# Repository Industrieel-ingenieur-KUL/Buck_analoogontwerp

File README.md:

# Buck_analoogontwerp
Buck converter project for analog design

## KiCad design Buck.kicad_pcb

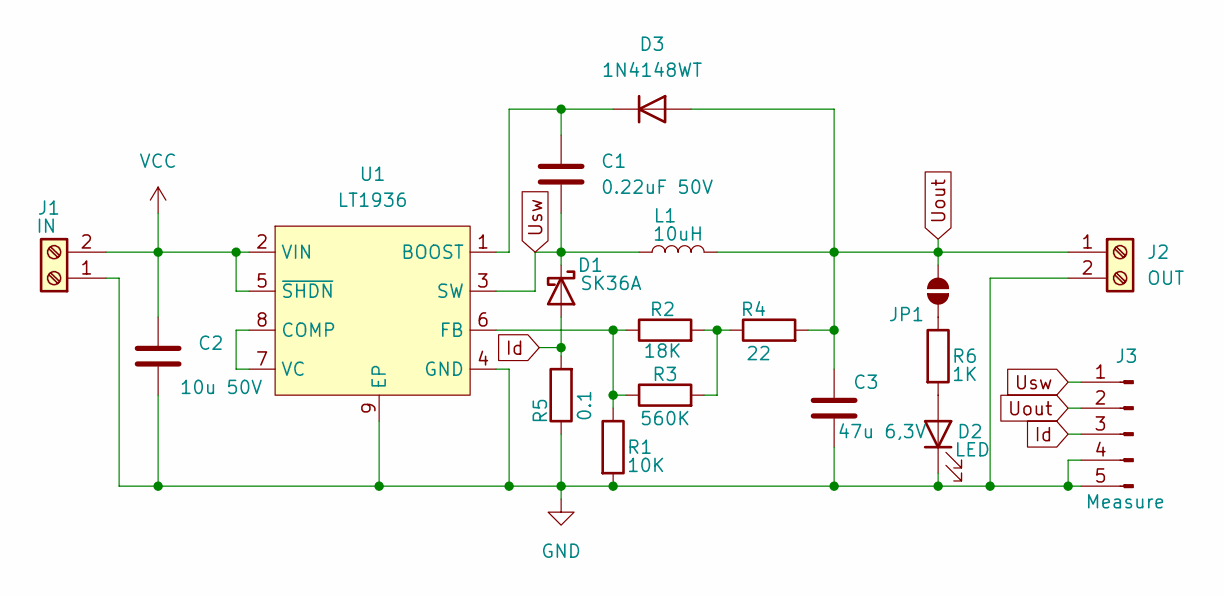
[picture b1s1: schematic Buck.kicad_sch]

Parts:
C1: 0.22uF 50V; C_0805_2012Metric_Pad1.18x1.45mm_HandSolder
C2: 10u 50V; C_1206_3216Metric_Pad1.33x1.80mm_HandSolder
C3: 47u 6,3V; C_1210_3225Metric_Pad1.33x2.70mm_HandSolder
D1: SK36A; D_SMC
D2: LED; LED_0805_2012Metric_Pad1.15x1.40mm_HandSolder
D3: 1N4148WT; D_SOD-523
J1: IN; TerminalBlock_MaiXu_MX126-5.0-02P_1x02_P5.00mm
J2: OUT; TerminalBlock_MaiXu_MX126-5.0-02P_1x02_P5.00mm
J3: Measure; PinHeader_1x05_P2.54mm_Vertical
JP1: SolderJumper_2_Open; SolderJumper-2_P1.3mm_Open_TrianglePad1.0x1.5mm
L1: 10uH; L_7.3x7.3_H4.5
R1: 10K; R_1206_3216Metric_Pad1.30x1.75mm_HandSolder
R2: 18K; R_1206_3216Metric_Pad1.30x1.75mm_HandSolder
R3: 560K; R_1206_3216Metric_Pad1.30x1.75mm_HandSolder
R4: 22; R_1206_3216Metric_Pad1.30x1.75mm_HandSolder
R5: 0.1; R_2010_5025Metric_Pad1.40x2.65mm_HandSolder
R6: 1K; R_1206_3216Metric_Pad1.30x1.75mm_HandSolder
U1: LT1936; MSOP-8-1EP_3x3mm_P0.65mm_EP1.95x2.15mm

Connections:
GND: C2.2, C3.2, D2.1 (K), J1.1, J2.2, J3.4, J3.5, R1.2, R5.1, U1.4 (GND), U1.9 (EP)
Id: D1.2 (A), J3.3, R5.2
unnamed: D2.2 (A), R6.2
unnamed: C1.1, D3.1 (K), U1.1 (BOOST)
unnamed: JP1.2 (B), R6.1
unnamed: R2.2, R3.2, R4.1
unnamed: U1.7 (VC), U1.8 (COMP)
unnamed: R1.1, R2.1, R3.1, U1.6 (FB)
Uout: C3.1, D3.2 (A), J2.1, J3.2, JP1.1 (A), L1.2, R4.2
Usw: C1.2, D1.1 (K), J3.1, L1.1, U1.3 (SW)
VCC: C2.1, J1.2, U1.2 (VIN), U1.5 (~SHDN)

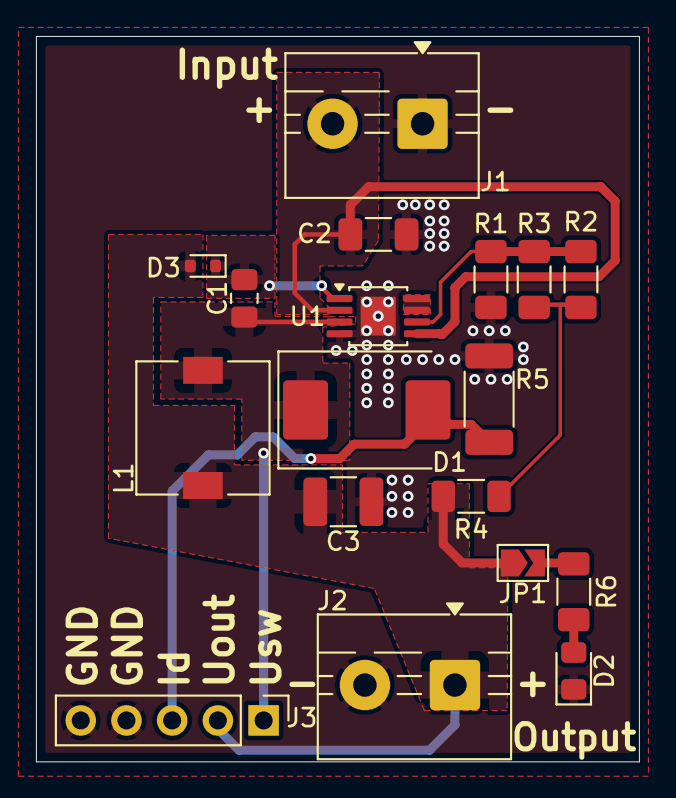
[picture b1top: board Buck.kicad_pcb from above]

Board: 2 copper layers, 33.5 x 40.3 mm, 18 parts (0 on the bottom side), 11 nets.

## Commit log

2025-11-01 added all files
2025-11-01 small tweaks trace layout
2025-11-05 addes extra silkscreen for info
2025-11-05 solder pad tweak
2025-11-06 added qr code to git
